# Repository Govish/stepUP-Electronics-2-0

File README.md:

# stepUP-Electronics-2-0
 New Electronics Suite for the stepUP 3D Printer!
 New Electronics include:
  - An updated LCD control panel loosely based off the Panelolu2
  - New printer mainboard
     - Arduino DUE printer controller running Marlin 2.0
     - ESP32 acting as WiFi server through ESP3D
     - Multiplexed SD card allowing read/write access to both the ESP32 and the Arduino DUE
     - TMC2130 Stepper Drivers with SPI configuration and connected diagnostic pins
     - RGB LED light strip control
     - High-power 20A heated bed control
     - ATX PSU control
  - Black ribbon cable wiring all throughout the machine with PCB breakouts
     - Full connectorization

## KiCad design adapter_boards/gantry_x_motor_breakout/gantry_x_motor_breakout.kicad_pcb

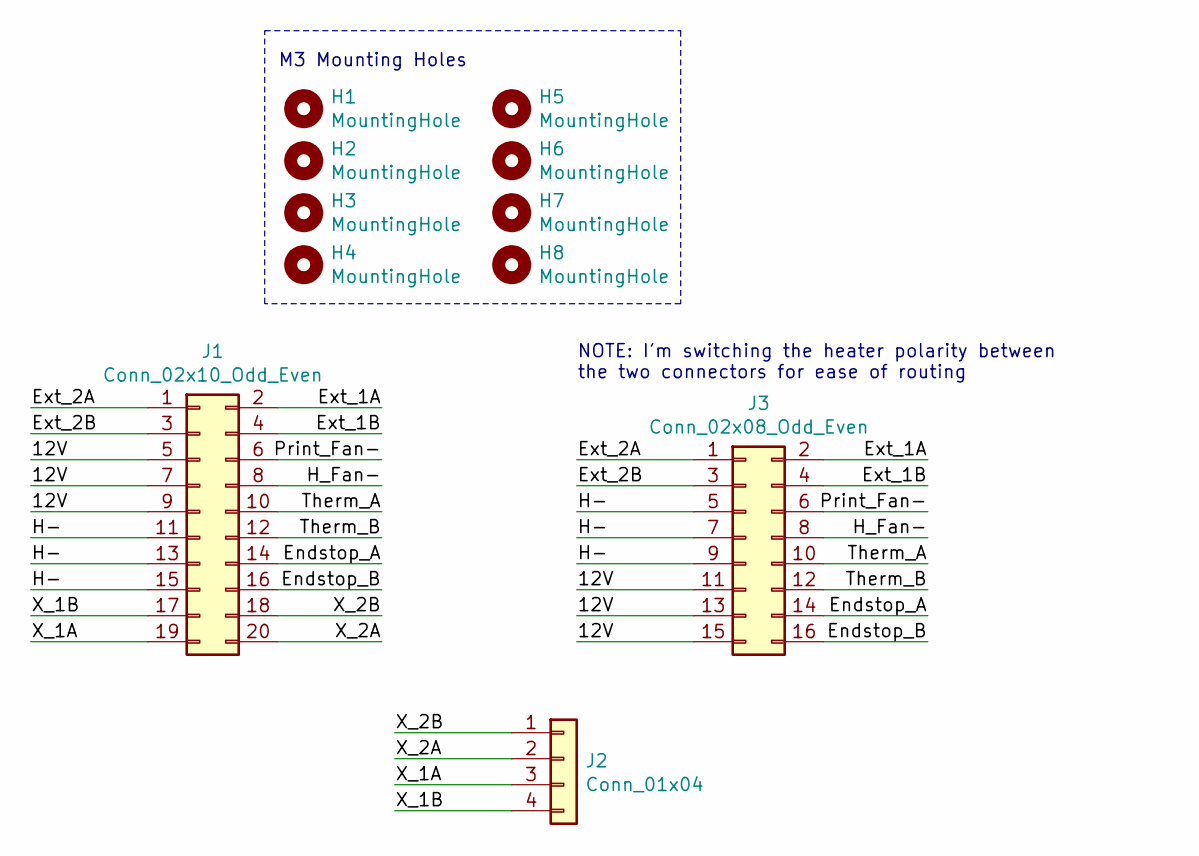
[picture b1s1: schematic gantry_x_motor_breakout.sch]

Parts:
H1, H2, H3, H4, H5, H6, H7, H8: MountingHole; MountingHole_3.2mm_M3_Pad
J1: Conn_02x10_Odd_Even; IDC-Header_2x10_P2.54mm_Vertical
J2: Conn_01x04; JST_XH_B4B-XH-A_1x04_P2.50mm_Vertical
J3: Conn_02x08_Odd_Even; IDC-Header_2x08_P2.54mm_Vertical

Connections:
/12V: J1.5, J1.7, J1.9, J3.11, J3.13, J3.15
/Endstop_A: J1.14, J3.14
/Endstop_B: J1.16, J3.16
/Ext_1A: J1.2, J3.2
/Ext_1B: J1.4, J3.4
/Ext_2A: J1.1, J3.1
/Ext_2B: J1.3, J3.3
/H-: J1.11, J1.13, J1.15, J3.5, J3.7, J3.9
/H_Fan-: J1.8, J3.8
/Print_Fan-: J1.6, J3.6
/Therm_A: J1.10, J3.10
/Therm_B: J1.12, J3.12
/X_1A: J1.19, J2.3
/X_1B: J1.17, J2.4
/X_2A: J1.20, J2.2
/X_2B: J1.18, J2.1

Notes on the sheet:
M3 Mounting Holes
NOTE: I'm switching the heater polarity between the two connectors for ease of routing

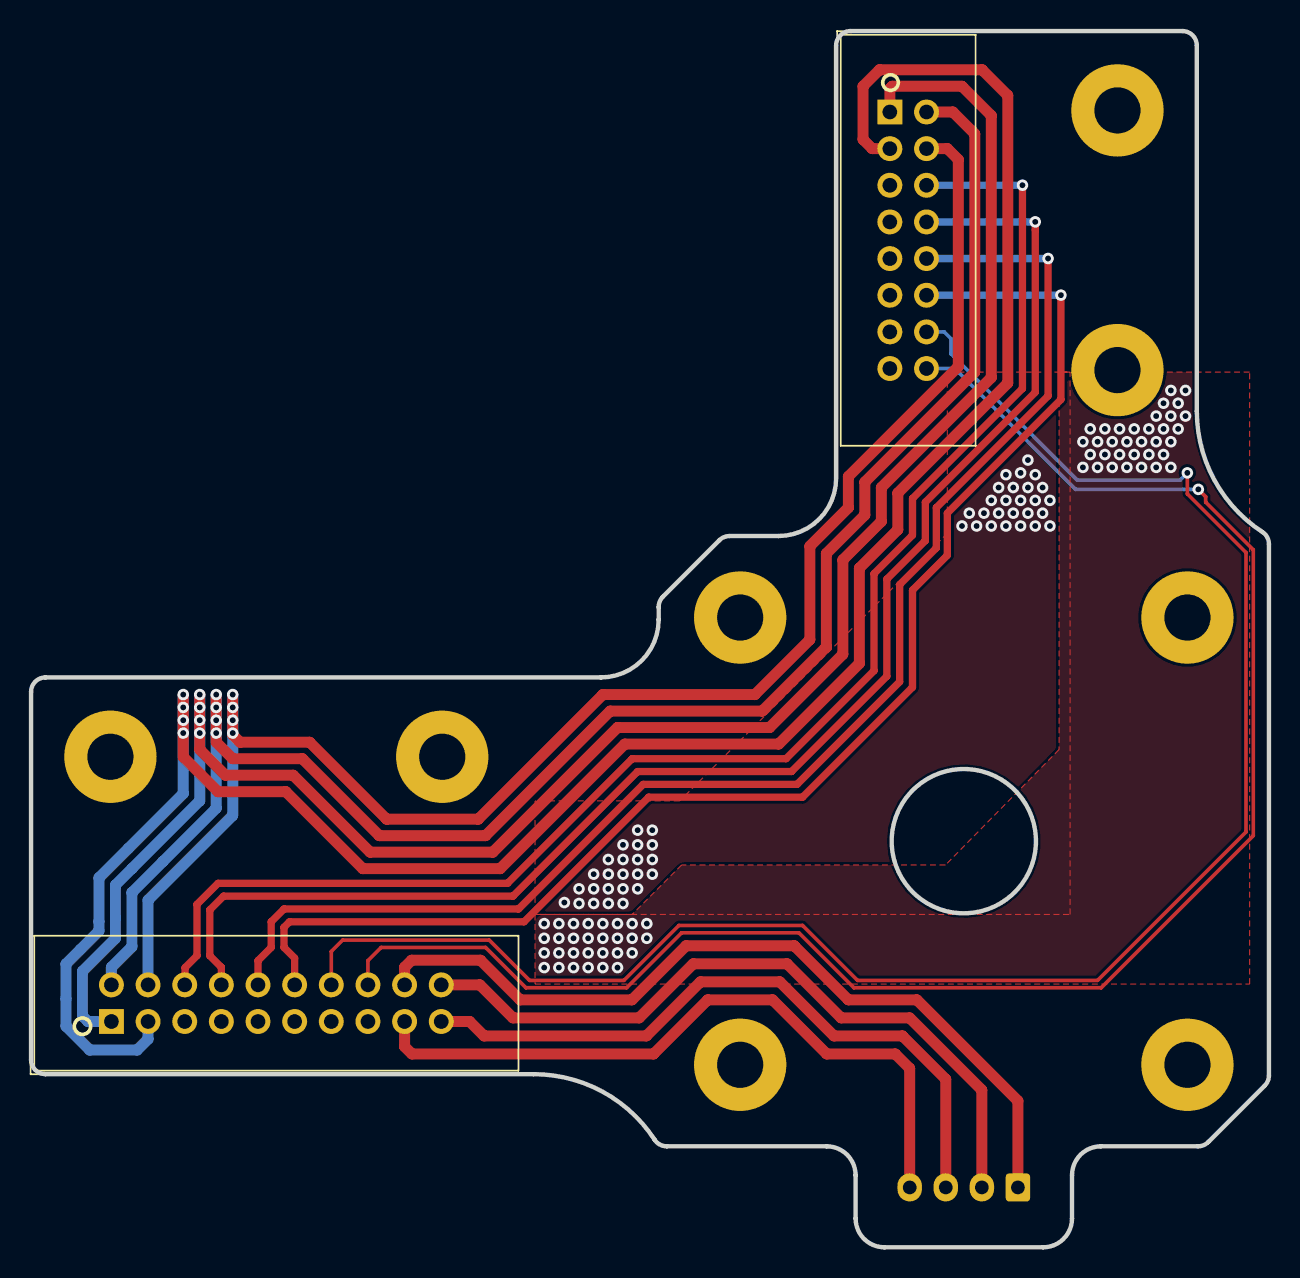
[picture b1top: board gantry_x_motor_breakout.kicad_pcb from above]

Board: 2 copper layers, 85.8 x 84.3 mm, 11 parts (1 on the bottom side), 16 nets.

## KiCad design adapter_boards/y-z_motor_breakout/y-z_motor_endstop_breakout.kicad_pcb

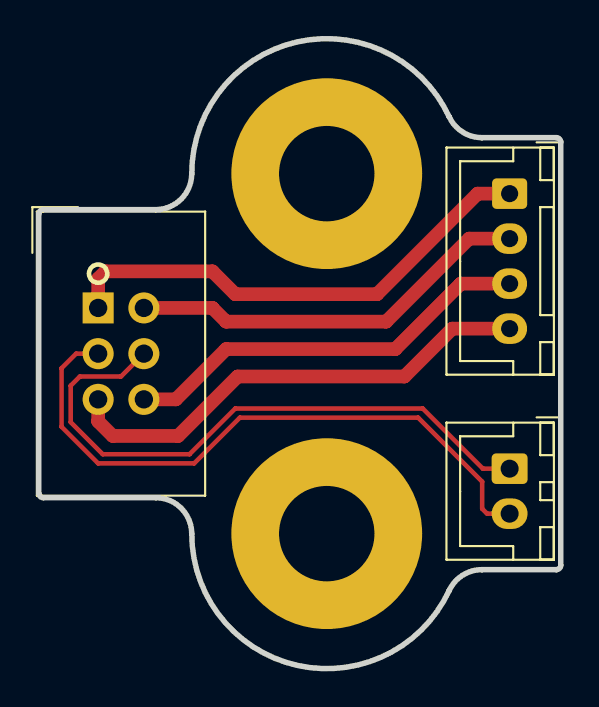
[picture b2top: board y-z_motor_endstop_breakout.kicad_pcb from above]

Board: 2 copper layers, 29.0 x 35.0 mm, 5 parts (0 on the bottom side), 6 nets.

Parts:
H1, H2: MountingHole; MountingHole_5.3mm_M5_Pad
J1: Conn_02x03_Odd_Even; IDC-Header_2x03_P2.54mm_Vertical
J2: Conn_01x04; JST_XH_B4B-XH-A_1x04_P2.50mm_Vertical
J3: Conn_01x02; JST_XH_B2B-XH-A_1x02_P2.50mm_Vertical

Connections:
unnamed: J1.1, J2.1
unnamed: J1.2, J2.2
unnamed: J1.3, J3.2
unnamed: J1.4, J3.1
unnamed: J1.5, J2.4
unnamed: J1.6, J2.3

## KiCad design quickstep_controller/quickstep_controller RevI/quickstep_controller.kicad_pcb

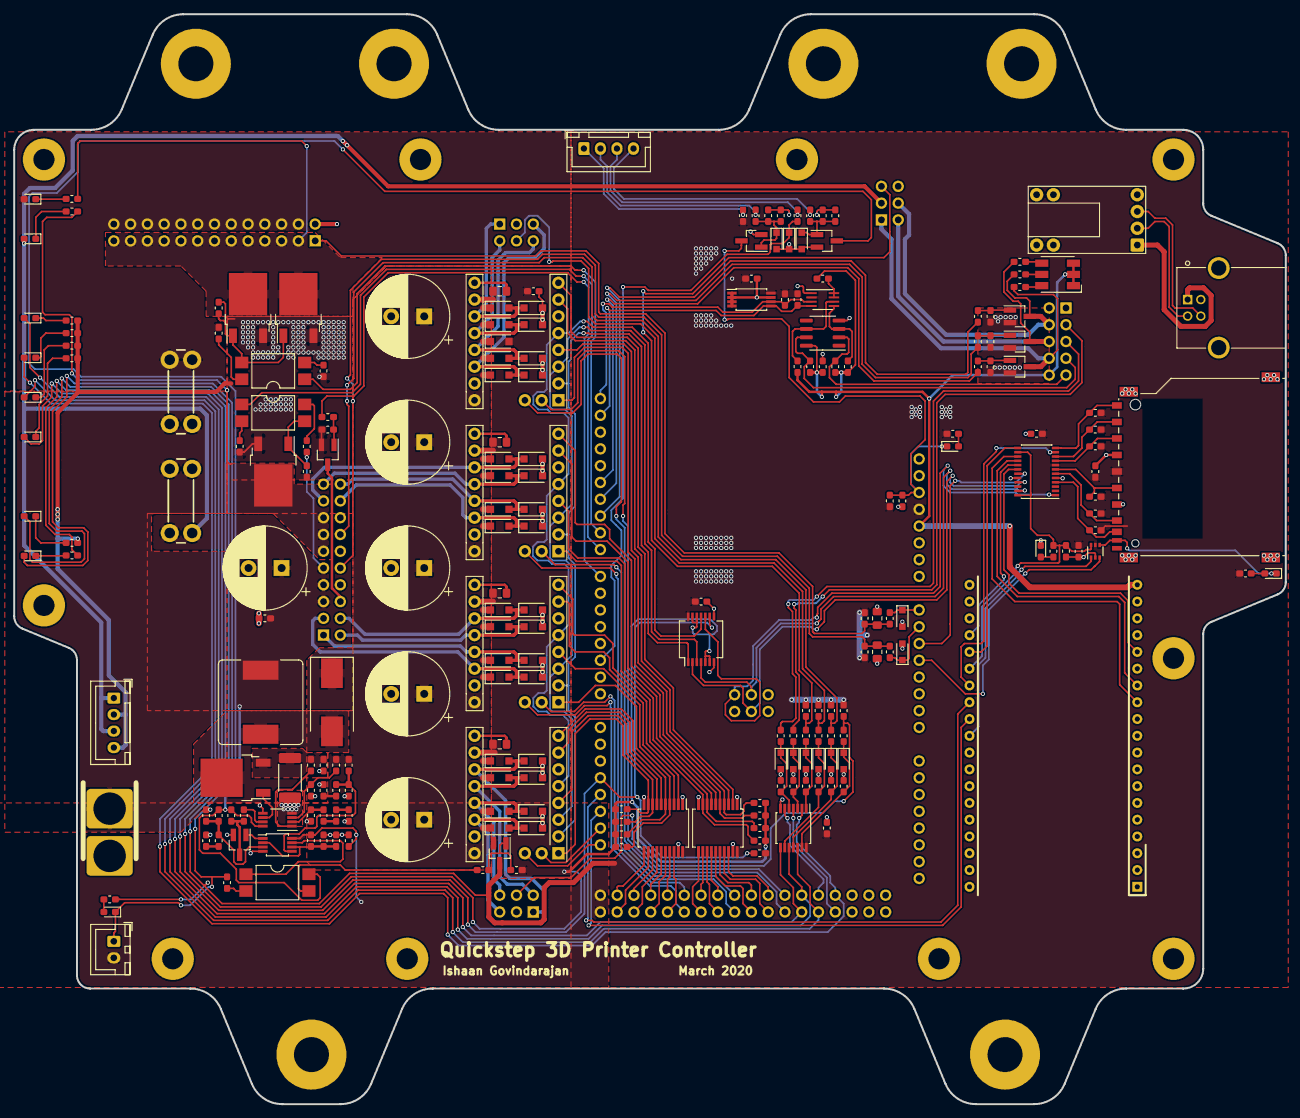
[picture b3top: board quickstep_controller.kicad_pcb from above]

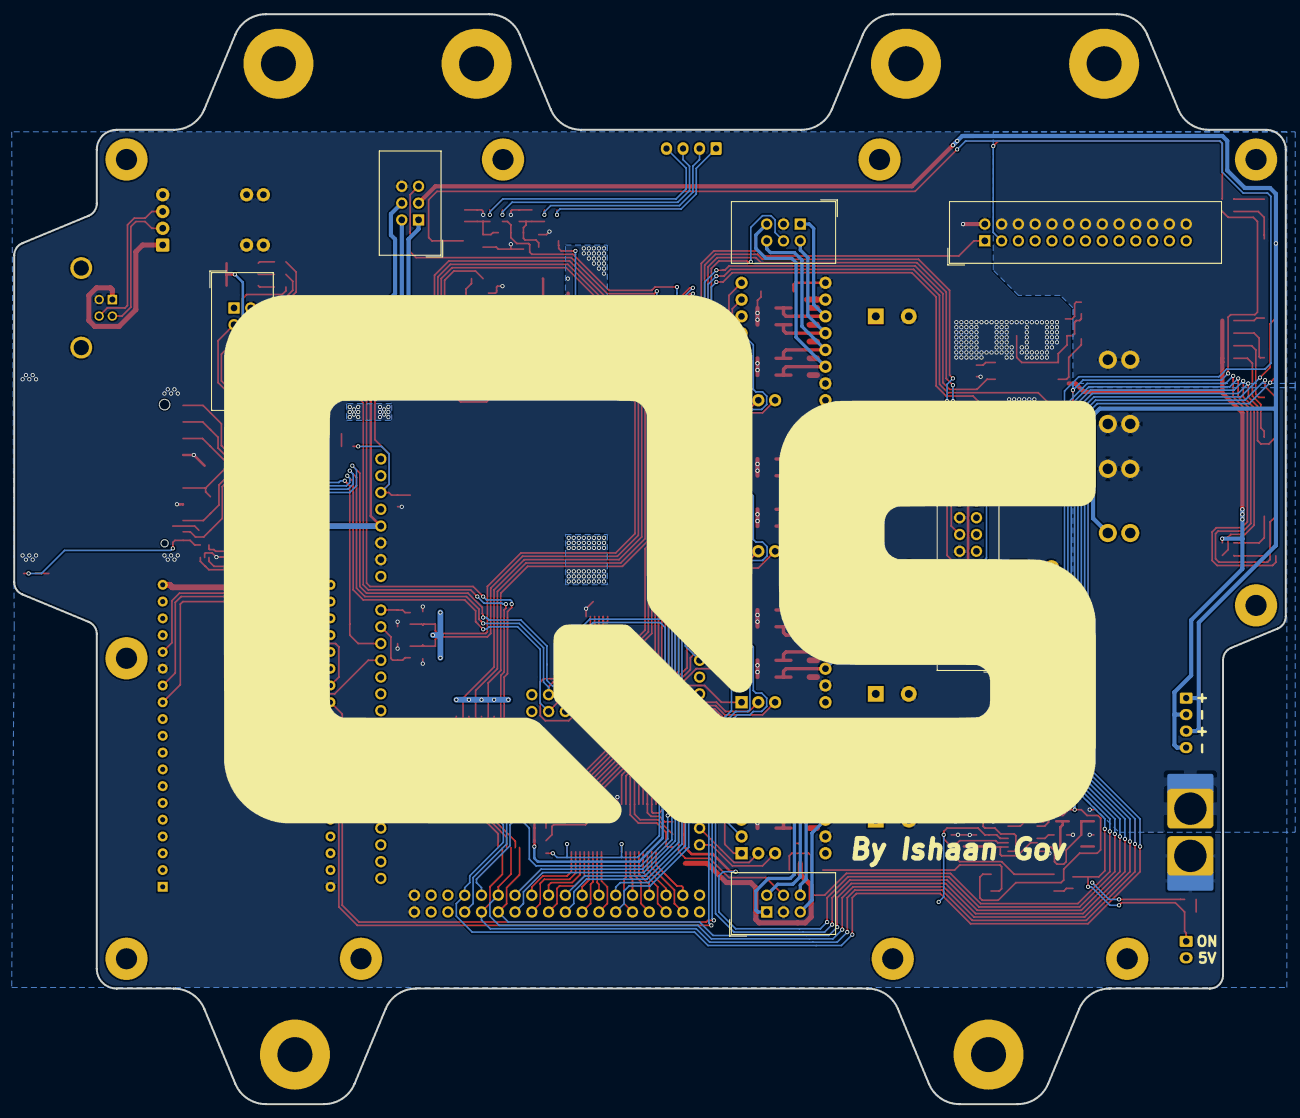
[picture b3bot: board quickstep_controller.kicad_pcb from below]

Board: 2 copper layers, 192.5 x 165.0 mm, 252 parts (8 on the bottom side), 188 nets.

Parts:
C201, C202, C203, C401, C402, C403, C404, C405, C406, C407, C408, C501, C502, C709, C801, C803, C804, C807, C809, C1201, C1202: 100n; C_0603_1608Metric_Pad1.05x0.95mm_HandSolder
C301, C302, C701, C703, C705, C707: 4u7; C_0805_2012Metric_Pad1.15x1.40mm_HandSolder
C702, C704, C706, C708, C802, C810: 470u; CP_Radial_D12.5mm_P5.00mm
C805: 270p; C_0603_1608Metric_Pad1.05x0.95mm_HandSolder
C806: 4.7n; C_0603_1608Metric_Pad1.05x0.95mm_HandSolder
C808: 10p; C_0603_1608Metric_Pad1.05x0.95mm_HandSolder
D201, D202, D301, D302, D405, D406, D407, D408, D409, D410, D702, D703: RED; LED_0603_1608Metric_Pad1.05x0.95mm_HandSolder
D303, D304, D401, D402, D403, D404, D411, D412, D413, D1201, D1202: 3.6V; D_SOD-323_HandSoldering
D501: 150505M173300; LED_RGB_5050-6
D701, D901, D902, D903, D904, D905, D906, D907, D908, D1001, D1002, D1003, D1004, D1005, D1006, D1007, D1008, D1401, D1402, D1403, D1404, D1405, D1406, D1407, D1408, D1409, D1410, D1411, D1412, D1413, D1414, D1415, D1416: DSS15UTR; D_SOD-123F
D801: CDBC380-G; D_SMC_Handsoldering
F1501: 7.5A; Keystone_3557
F1502: 25A; Keystone_3557
G101: Quickstep Logo; qs_logo
H101, H102, H103, H104, H105, H106, H107, H108, H109, H110: M3; MountingHole_3.2mm_M3_Pad
H111, H112, H113, H114, H115, H116: M5; MountingHole_5.3mm_M5_Pad
J101, J1502: Conn_01x04; JST_XH_B4B-XH-A_1x04_P2.50mm_Vertical
J201: SD_Card; SD_TE_2041021
J601: USB_A; USB_Adapter
J602: USB_B; CUI_UJ2-BH-W1-TH
J901, J1001, J1301: Conn_02x03_Odd_Even; IDC-Header_2x03_P2.54mm_Vertical
J1101: Conn_02x13_Odd_Even; IDC-Header_2x13_P2.54mm_Vertical
J1201: Conn_02x05_Odd_Even; IDC-Header_2x05_P2.54mm_Vertical
J1401: Conn_02x10_Odd_Even; IDC-Header_2x10_P2.54mm_Vertical
J1501: Conn_01x02; JST_XH_B2B-XH-A_1x02_P2.50mm_Vertical
J1503: Conn_XT; XT60-Male
L801: 4.7uH; L_Bourns_SRR1260
Q301, Q302, Q304, Q802: AOD514; TO-252-2
Q303, Q401, Q402, Q501, Q502, Q503, Q701, Q801: NTR3C21NZT1G; SOT-23_Handsoldering
R201, R202, R301, R302, R409, R410, R411, R412, R413, R417, R418, R419, R420, R421, R514, R515, R516, R712, R715, R803, R805, R807, R808, R816: 1K; R_0603_1608Metric_Pad1.05x0.95mm_HandSolder
R203, R204, R205, R206, R207, R208, R209, R401, R402, R403, R404, R405, R406, R407, R408, R414, R701, R702, R703, R704, R705, R706, R707, R708, R710, R713, R714, R804, R809, R810, R811, R1201, R1202: 10K; R_0603_1608Metric_Pad1.05x0.95mm_HandSolder
R303, R311, R312, R506, R507, R508, R509, R510, R709, R711: 390; R_0603_1608Metric_Pad1.05x0.95mm_HandSolder
R304, R306: 390R; R_0603_1608Metric_Pad1.05x0.95mm_HandSolder
R305, R307, R308, R415, R416, R503, R511, R512, R513: 240K; R_0603_1608Metric_Pad1.05x0.95mm_HandSolder
R309, R310, R313, R314, R501, R502, R504, R505: 4K7; R_0603_1608Metric_Pad1.05x0.95mm_HandSolder
R801, R806, R812: 16.9K; R_0603_1608Metric_Pad1.05x0.95mm_HandSolder
R802: 4.7K; R_0603_1608Metric_Pad1.05x0.95mm_HandSolder
R813: 100R; R_0603_1608Metric_Pad1.05x0.95mm_HandSolder
R814: 7mR; R_2512_6332Metric_Pad1.52x3.35mm_HandSolder
R815: 22.6K; R_0603_1608Metric_Pad1.05x0.95mm_HandSolder
U201: TS3A27518E; TSSOP-24_4.4x7.8mm_P0.65mm
U202: SN74LVC1G3157DCK3; SOT-363_SC-70-6
U301, U302, U708: LTV-817S; SMDIP-4_W9.53mm
U401: 74HC14; TSSOP-14_4.4x5mm_P0.65mm
U501: PCA9306; SSOP-8_2.95x2.8mm_P0.65mm
U502: P82B715; SOIC-8_3.9x4.9mm_P1.27mm
U503: 24LC256; TSSOP-8_4.4x3mm_P0.65mm
U601: ESP-32_DEVBOARD; ESP32
U701, U702, U703, U704: StepStick-TMC2130; TMC-21x0
U705: 4066; SSOP-14_5.3x6.2mm_P0.65mm
U706, U707: 74HC245; SSOP-20_5.3x7.2mm_P0.65mm
U801: LM3488; VSSOP-8_3.0x3.0mm_P0.65mm
U802: LM393; MSOP-8_3x3mm_P0.65mm
XA601: Arduino_Due_Shield; Arduino_Due_Shield_noHolesSilk

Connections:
+3V3: C201.2, C202.1, C203.1, C405.2, C502.2, C709.2, D702.2, J201.4, Q701.3, R201.2, R204.2, R205.2, R206.2, R207.2, R208.2, R209.2, R313.1, R314.1, R401.1, R402.1, R403.1, R404.1, R413.2, R414.1, R417.2, R418.2, R501.2, R502.2, R710.1, U201.8, U202.5, U401.14, U501.2, U503.8, U705.14, U706.20, U707.20, XA601.3V3
+5V: C501.2, C809.2, D501.1, D501.2, D501.3, J1201.10, J1501.2, R503.1, R504.2, R505.2, R506.2, R507.2, R809.1, U502.8, U601.19, U802.8, XA601.5V1, XA601.5V3, XA601.5V4
+12V: C802.1, C803.1, D301.2, F1501.1, J1301.3, J1401.5, J1401.7, J1401.9, J1502.1, J1502.3, L801.1, R306.2, R801.1, R811.1, U708.4, U801.8
/ATX_Connections/LINE_IN: F1501.2, F1502.2, J1503.+
/ATX_Connections/PS_ON: D410.1, J1501.1, Q402.3, R715.2
/ENC_A: U401.6, XA601.D46
/ENC_B: U401.4, XA601.D49
/EXT-: J1401.11, J1401.13, J1401.15, Q302.2, R309.2
/FIL_SEN+: J901.4, R404.2, R408.1
/PRINT_FAN-: J1401.6, Q303.3
/THERM+: C302.1, J1401.10, R312.1, R314.2
/X_STOP+: J1401.14, R401.2, R405.1
/Y_STOP+: J1301.5, R402.2, R406.1
/Z_STOP+: J1001.4, R403.2, R407.1
/qs_Drivers/BUF_ECS: R704.1, U704.4, U706.4
/qs_Drivers/BUF_EDIR: U704.8, U706.2
/qs_Drivers/BUF_EEN: R708.2, U704.1, U706.5
/qs_Drivers/BUF_ESTEP: U704.7, U706.3
/qs_Drivers/BUF_XCS: R701.1, U701.4, U707.8
/qs_Drivers/BUF_XDIR: U701.8, U707.6
/qs_Drivers/BUF_XEN: R705.2, U701.1, U707.9
/qs_Drivers/BUF_XSTEP: U701.7, U707.7
/qs_Drivers/BUF_YCS: R702.1, U702.4, U707.4
/qs_Drivers/BUF_YDIR: U702.8, U707.2
/qs_Drivers/BUF_YEN: R706.2, U702.1, U707.5
/qs_Drivers/BUF_YSTEP: U702.7, U707.3
/qs_Drivers/BUF_ZCS: R703.1, U703.4, U706.8
/qs_Drivers/BUF_ZDIR: U703.8, U706.6
/qs_Drivers/BUF_ZEN: R707.2, U703.1, U706.9
/qs_Drivers/BUF_ZSTEP: U703.7, U706.7
/qs_Drivers/DUE_MISO: U201.1, U705.10, XA601.MISO
/qs_Drivers/DUE_MOSI: U201.21, U705.2, XA601.MOSI
/qs_Drivers/DUE_SCK: U201.23, U705.4, XA601.SCK
/qs_Drivers/DUE_VMOT_GOOD: R709.1, R710.2, U705.9, U706.19, U707.19, XA601.D17
/qs_Drivers/ECS: U706.16, XA601.D27
/qs_Drivers/EDIAG0: U704.18, XA601.D30
/qs_Drivers/EDIAG1: U704.17, XA601.D31
/qs_Drivers/EDIR: U706.18, XA601.D29
/qs_Drivers/EEN: U706.15, XA601.D26
/qs_Drivers/ESTEP: U706.17, XA601.D28
/qs_Drivers/VMOT_GOOD: U708.1, U802.7
/qs_Drivers/XCS: U707.12, XA601.D32
/qs_Drivers/XDIAG0: U701.18, XA601.D36
/qs_Drivers/XDIAG1: U701.17, XA601.D37
/qs_Drivers/XDIR: U707.14, XA601.D34
/qs_Drivers/XEN: U707.11, XA601.D33
/qs_Drivers/XSTEP: U707.13, XA601.D35
/qs_Drivers/X_1A: D1403.2, D1404.1, J1401.19, U701.12
/qs_Drivers/X_1B: D1407.2, D1408.1, J1401.17, U701.11
/qs_Drivers/X_2A: D1415.2, D1416.1, J1401.20, U701.13
/qs_Drivers/X_2B: D1411.2, D1412.1, J1401.18, U701.14
/qs_Drivers/YCS: U707.16, XA601.D38
/qs_Drivers/YDIAG0: U702.18, XA601.D42
/qs_Drivers/YDIAG1: U702.17, XA601.D43
/qs_Drivers/YDIR: U707.18, XA601.D40
/qs_Drivers/YEN: U707.15, XA601.D39
/qs_Drivers/YSTEP: U707.17, XA601.D41
/qs_Drivers/ZCS: U706.12, XA601.D23
/qs_Drivers/ZDIAG0: U703.18, XA601.D20
/qs_Drivers/ZDIAG1: U703.17, XA601.D21
/qs_Drivers/ZDIR: U706.14, XA601.D25
/qs_Drivers/ZEN: U706.11, XA601.D22
/qs_Drivers/ZSTEP: U706.13, XA601.D24
/qs_Drivers/_MISO: U701.5, U702.5, U703.5, U704.5, U705.11
/qs_Drivers/_MOSI: U701.2, U702.2, U703.2, U704.2, U705.1
/qs_Drivers/_SCK: U701.3, U702.3, U703.3, U704.3, U705.3
/qs_I2C_LEDs/B_DRAIN: J1201.8, J1301.1, Q503.3, R516.2
/qs_I2C_LEDs/B_PWM: R510.2, XA601.D12
/qs_I2C_LEDs/DUE_SCL: R501.1, U501.3, U503.6, XA601.SCL1
/qs_I2C_LEDs/DUE_SDA: R502.1, U501.4, U503.5, XA601.SDA1
/qs_I2C_LEDs/G_DRAIN: J1201.6, J1301.2, Q502.3, R514.2
/qs_I2C_LEDs/LCL: J1201.7, R507.1, U502.7
/qs_I2C_LEDs/LDA: J1201.9, R506.1, U502.2
/qs_LCD/LED_RED: J1201.4, J1301.4, Q501.3, R515.2
/qs_Processors/D+: J601.3, J602.3
/qs_Processors/D-: J601.2, J602.2
/qs_Processors/DUE_EXT_HEAT: U302.1, XA601.D8
/qs_Processors/DUE_EXT_THERM: D304.1, R312.2, XA601.A1
/qs_Processors/DUE_LED_GREEN: R509.2, XA601.D11
/qs_Processors/DUE_LED_RED: R508.2, XA601.D10
/qs_Processors/DUE_PC_FAN: R303.2, XA601.D7
/qs_Processors/DUE_PSON: D413.1, R420.2, XA601.D2
/qs_Processors/DUE_RESET: C406.2, D409.1, Q401.3, R414.2, XA601.RST1
/qs_Processors/ESP_CD: U202.1, U601.29
/qs_Processors/ESP_CLK: U201.15, U601.12
/qs_Processors/ESP_CMD: U201.17, U601.23
/qs_Processors/ESP_D0: U201.13, U601.24
/qs_Processors/ESP_D1: U201.11, U601.26
/qs_Processors/ESP_D2: U201.16, U601.13
/qs_Processors/ESP_D3: U201.18, U601.15
/qs_Processors/ESP_RX: U601.27, XA601.D18
/qs_Processors/ESP_SD_SEL: R202.2, R203.2, U201.14, U201.24, U202.6, U601.25
/qs_Processors/ESP_TX: U601.28, XA601.D19
/qs_Processors/FIL_RUNOUT: D408.2, U401.8, XA601.D45
/qs_Processors/X_STOP: D405.2, U401.10, XA601.D44
/qs_Processors/Y_STOP: D406.2, U401.2, XA601.D48
/qs_Processors/Z_STOP: D407.2, U401.12, XA601.D47
/qs_SD_Interface/CARD_DETECT: D202.1, J201.10, U202.4
/qs_SD_Interface/CLK: J201.5, R207.1, U201.7
/qs_SD_Interface/CMD: J201.2, R206.1, U201.9
/qs_SD_Interface/D0: J201.7, R208.1, U201.6
/qs_SD_Interface/D1: J201.8, R209.1, U201.4
/qs_SD_Interface/D2: J201.9, R204.1, U201.12
/qs_SD_Interface/D3: J201.1, R205.1, U201.10
/qs_SD_Interface/DUE_CD: U202.3, XA601.A3
/qs_SD_Interface/DUE_CS: U201.19, XA601.A2
/qs_Switches/E_PS_ON_IN: J101.4, R421.1
/qs_Switches/E_PS_ON_OUT: J101.3, R420.1
/qs_Switches/E_RST_IN: J101.2, R419.1
/qs_Switches/E_RST_OUT: J101.1, R418.1
/qs_Temp_Control/BED_HEAT: U301.1, XA601.D9
/qs_Temp_Control/BED_THERM: D303.1, R311.2, XA601.A0
/qs_bed_conn/BED-: J1101.3, J1101.5, J1101.7, J1101.9, J1101.11, J1101.13, J1101.15, J1101.17, J1101.19, J1101.21, J1101.23, J1101.25, Q301.2, Q304.2, R310.2
/qs_bed_conn/THERM+: C301.1, J1101.1, R311.1, R313.2
/qs_gantry_conn/EXT_1A: D1413.2, D1414.1, J1401.2, U704.12
/qs_gantry_conn/EXT_1B: D1409.2, D1410.1, J1401.4, U704.11
/qs_gantry_conn/EXT_2A: D1401.2, D1402.1, J1401.1, U704.13
/qs_gantry_conn/EXT_2B: D1405.2, D1406.1, J1401.3, U704.14
/qs_power/EN_CONV: Q801.1, U802.1
/qs_power/SENSE: C808.1, Q802.3, R813.2, R814.1
/qs_power/SWITCH: D801.2, L801.2, Q802.2
/qs_ymotor_fil/YMOT_1A: D905.2, D906.1, J901.2, U702.12
/qs_ymotor_fil/YMOT_1B: D901.2, D902.1, J901.1, U702.11
/qs_ymotor_fil/YMOT_2A: D907.2, D908.1, J901.6, U702.13
/qs_ymotor_fil/YMOT_2B: D903.2, D904.1, J901.5, U702.14
/qs_zmotor_stop/ZMOT_1A: D1005.2, D1006.1, J1001.2, U703.12
/qs_zmotor_stop/ZMOT_1B: D1001.2, D1002.1, J1001.1, U703.11
/qs_zmotor_stop/ZMOT_2A: D1007.2, D1008.1, J1001.6, U703.13
/qs_zmotor_stop/ZMOT_2B: D1003.2, D1004.1, J1001.5, U703.14
GND: C201.1, C202.2, C203.2, C301.2, C302.2, C401.2, C402.2, C403.2, C404.2, C405.1, C406.1, C407.1, C408.1, C501.1, C502.1, C701.1, C702.2, C703.1, C704.2, C705.1, C706.2, C707.1, C708.2, C709.1, C801.1, C802.2, C803.2, C804.1, C805.1, C807.1, C808.2, C809.1, C810.2, C1201.2, C1202.2, D201.1, D303.2, D304.2, D401.2, D402.2, D403.2, D404.2, D411.2, D412.2, D413.2, D902.2, D904.2, D906.2, D908.2, D1002.2, D1004.2, D1006.2, D1008.2, D1201.2, D1202.2, D1402.2, D1404.2, D1406.2, D1408.2, D1410.2, D1412.2, D1414.2, D1416.2, J201.3, J201.6, J201.12, J601.4, J601.5, J602.4, J602.5, J901.3, J1001.3, J1101.2, J1201.2, J1301.6, J1401.8, J1401.12, J1401.16, J1502.2, J1502.4, J1503.-, Q301.3, Q302.3, Q303.2, Q304.3, Q401.2, Q402.2, Q501.2, Q502.2, Q503.2, Q801.2, R203.1, R301.2, R302.2, R305.1, R307.1, R308.1, R409.1, R410.1, R411.1, R412.1, R415.1, R416.1, R511.1, R512.1, R513.1, R711.1, R712.2, R803.2, R805.2, R808.2, R810.2, R814.2, R816.2, U201.5, U201.20, U202.2, U401.7, U501.1, U502.4, U503.1, U503.2, U503.3, U503.4, U503.7, U601.14, U601.32, U601.38, U701.9, U701.15, U702.9, U702.15, U703.9, U703.15, U704.9, U704.15, U705.7, U705.8, U706.1, U706.10, U707.1, U707.10, U801.4, U801.5, U802.4, XA601.GND2, XA601.GND3, XA601.GND5, XA601.GND6
unnamed: C401.1, D401.1, R405.2, U401.11
unnamed: C402.1, D402.1, R406.2, U401.1
unnamed: C403.1, D403.1, R407.2, U401.13
unnamed: C404.1, D404.1, R408.2, U401.9
unnamed: C407.2, D411.1, Q401.1, R415.2, R419.2
unnamed: C408.2, D412.1, Q402.1, R416.2, R421.2
unnamed: C801.2, R801.2, R802.1, U802.3
unnamed: C804.2, R806.2, R807.1, U802.5
unnamed: C805.2, C806.1, U801.2
unnamed: C806.2, R804.1
unnamed: C807.2, R809.2, R810.1, U802.2, U802.6
unnamed: C1201.1, D1201.1, R1201.2, U401.3
unnamed: C1202.1, D1202.1, R1202.2, U401.5
unnamed: D201.2, R202.1
unnamed: D202.2, R201.1
unnamed: D301.1, R309.1
unnamed: D302.1, R310.1
unnamed: D405.1, R409.2
unnamed: D406.1, R410.2
unnamed: D407.1, R411.2
unnamed: D408.1, R412.2
unnamed: D409.2, R413.1
unnamed: D410.2, R417.1
unnamed: D501.4, R514.1
unnamed: D501.5, R515.1
unnamed: D501.6, R516.1
unnamed: D702.1, R709.2
unnamed: D703.1, R711.2
unnamed: J601.1, J602.1
unnamed: J1201.3, R1201.1
unnamed: J1201.5, R1202.1
unnamed: Q301.1, Q304.1, R305.2, U301.3
unnamed: Q302.1, R307.2, U302.3
unnamed: Q303.1, R303.1, R308.2
unnamed: Q501.1, R508.1, R511.2
unnamed: Q502.1, R509.1, R512.2
unnamed: Q503.1, R510.1, R513.2
unnamed: Q701.1, R713.1, R714.2
unnamed: Q801.3, R811.2, R812.2
unnamed: Q802.1, U801.6
unnamed: R301.1, U301.2
unnamed: R302.1, U302.2
unnamed: R304.1, U301.4
unnamed: R306.1, U302.4
unnamed: R503.2, U501.7, U501.8
unnamed: R504.1, U501.5, U502.3
unnamed: R505.1, U501.6, U502.6
unnamed: R713.2, U708.3
unnamed: R715.1, U708.2
unnamed: R802.2, R803.1
unnamed: R804.2, R805.1
unnamed: R807.2, R808.1
unnamed: R812.1, U801.7
unnamed: R813.1, U801.1
unnamed: R815.2, R816.1, U801.3
VBUS: C702.1, C704.1, C706.1, C708.1, C810.1, D701.1, D801.1, D901.1, D903.1, D905.1, D907.1, D1001.1, D1003.1, D1005.1, D1007.1, D1401.1, D1403.1, D1405.1, D1407.1, D1409.1, D1411.1, D1413.1, D1415.1, R806.1, R815.1, U701.16, U702.16, U703.16, U704.16
VCC: C701.2, C703.2, C705.2, C707.2, D701.2, D703.2, Q701.2, R701.2, R702.2, R703.2, R704.2, R705.1, R706.1, R707.1, R708.1, R712.1, R714.1, U701.10, U702.10, U703.10, U704.10, U705.5, U705.6, U705.12, U705.13
VPP: D302.2, F1502.1, J1101.4, J1101.6, J1101.8, J1101.10, J1101.12, J1101.14, J1101.16, J1101.18, J1101.20, J1101.22, J1101.24, J1101.26, R304.2

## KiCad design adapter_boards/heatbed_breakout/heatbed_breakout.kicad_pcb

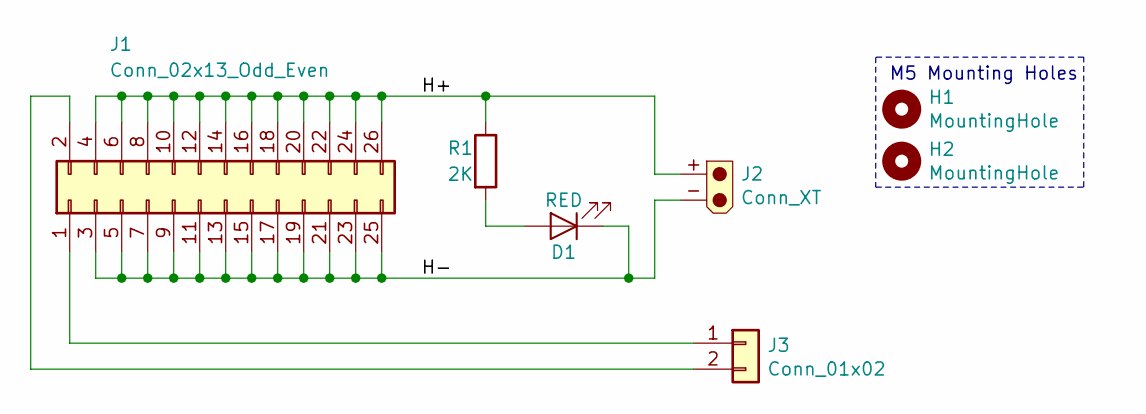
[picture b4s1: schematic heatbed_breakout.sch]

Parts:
D1: RED; LED_0603_1608Metric_Pad1.05x0.95mm_HandSolder
H1, H2: MountingHole; MountingHole_5.3mm_M5_Pad
J1: Conn_02x13_Odd_Even; IDC-Header_2x13_P2.54mm_Vertical
J2: Conn_XT; XT60-Female
J3: Conn_01x02; JST_XH_B2B-XH-A_1x02_P2.50mm_Vertical
R1: 2K; R_0603_1608Metric_Pad1.05x0.95mm_HandSolder

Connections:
/H+: J1.4, J1.6, J1.8, J1.10, J1.12, J1.14, J1.16, J1.18, J1.20, J1.22, J1.24, J1.26, J2.+, R1.1
/H-: D1.1 (K), J1.3, J1.5, J1.7, J1.9, J1.11, J1.13, J1.15, J1.17, J1.19, J1.21, J1.23, J1.25, J2.-
unnamed: D1.2 (A), R1.2
unnamed: J1.1, J3.1
unnamed: J1.2, J3.2

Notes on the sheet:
M5 Mounting Holes

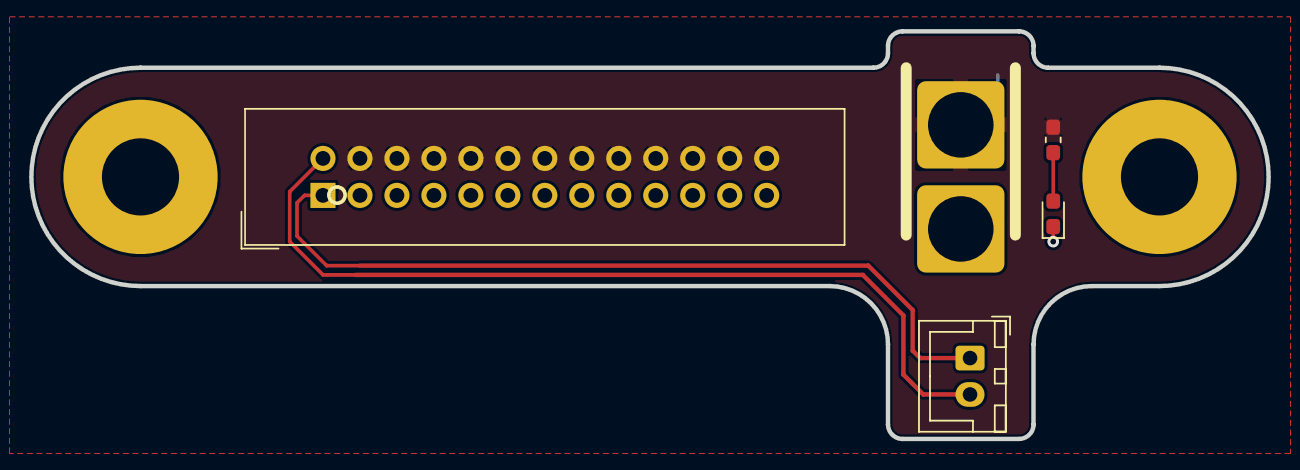
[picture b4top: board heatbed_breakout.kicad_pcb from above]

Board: 2 copper layers, 85.0 x 28.0 mm, 7 parts (0 on the bottom side), 5 nets.

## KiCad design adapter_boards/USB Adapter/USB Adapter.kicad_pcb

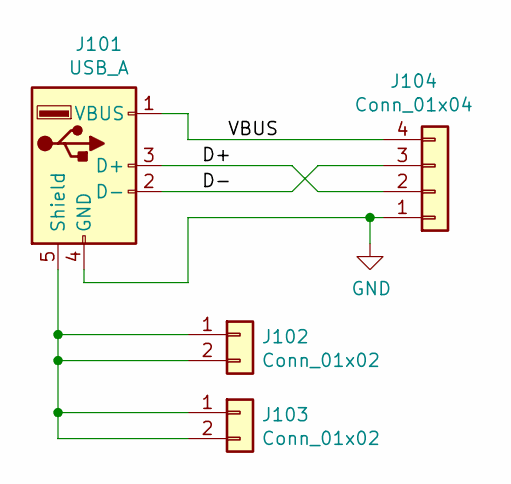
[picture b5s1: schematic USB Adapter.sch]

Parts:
J101: USB_A; USB_A_CNC_Tech-1001-008B-01001
J102, J103: Conn_01x02; PinHeader_1x02_P2.54mm_Vertical
J104: Conn_01x04; PinHeader_1x04_P2.54mm_Vertical

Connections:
/D+: J101.3 (D+), J104.2
/D-: J101.2 (D-), J104.3
/VBUS: J101.1 (VBUS), J104.4
GND: J101.4 (GND), J104.1
unnamed: J101.5 (Shield), J102.1, J102.2, J103.1, J103.2

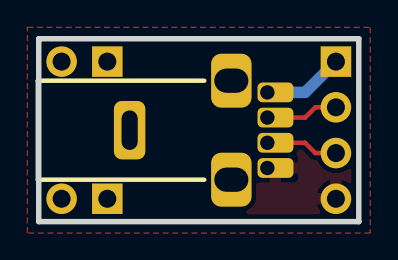
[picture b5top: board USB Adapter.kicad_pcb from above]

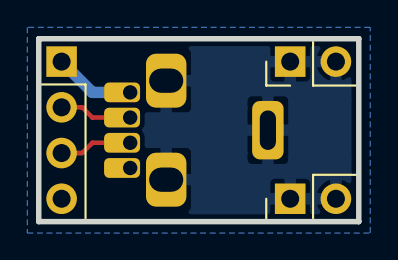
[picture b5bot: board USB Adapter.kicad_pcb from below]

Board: 2 copper layers, 17.8 x 10.2 mm, 4 parts (3 on the bottom side), 5 nets.

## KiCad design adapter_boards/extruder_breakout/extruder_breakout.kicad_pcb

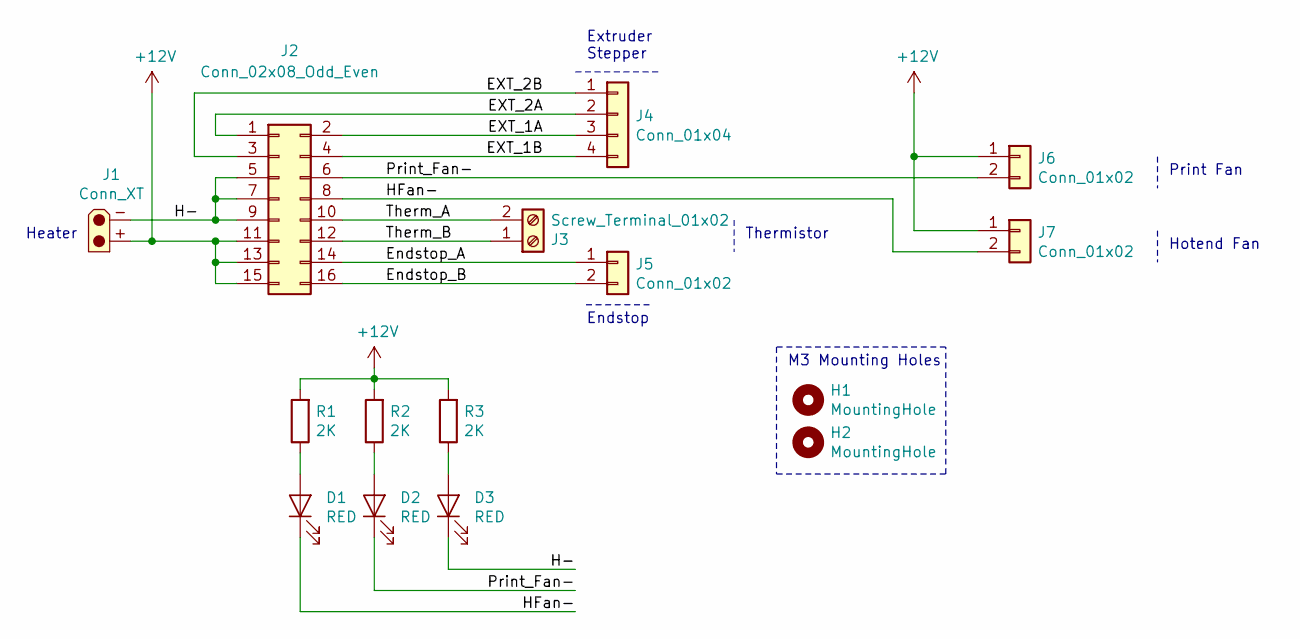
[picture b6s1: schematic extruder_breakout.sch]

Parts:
D1, D2, D3: RED; LED_0603_1608Metric_Pad1.05x0.95mm_HandSolder
H1, H2: MountingHole; MountingHole_3.2mm_M3_Pad
J1: Conn_XT; XT30U-F
J2: Conn_02x08_Odd_Even; IDC-Header_2x08_P2.54mm_Vertical
J3: Screw_Terminal_01x02; TerminalBlock_TE_2.54mmx02
J4: Conn_01x04; JST_XH_B4B-XH-A_1x04_P2.50mm_Vertical
J5, J6, J7: Conn_01x02; JST_XH_B2B-XH-A_1x02_P2.50mm_Vertical
R1, R2, R3: 2K; R_0603_1608Metric_Pad1.05x0.95mm_HandSolder

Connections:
+12V: J1.+, J2.11, J2.13, J2.15, J6.1, J7.1, R1.2, R2.2, R3.2
/EXT_1A: J2.2, J4.3
/EXT_1B: J2.4, J4.4
/EXT_2A: J2.1, J4.2
/EXT_2B: J2.3, J4.1
/Endstop_A: J2.14, J5.1
/Endstop_B: J2.16, J5.2
/H-: D3.1 (K), J1.-, J2.5, J2.7, J2.9
/HFan-: D1.1 (K), J2.8, J7.2
/Print_Fan-: D2.1 (K), J2.6, J6.2
/Therm_A: J2.10, J3.2
/Therm_B: J2.12, J3.1
unnamed: D1.2 (A), R1.1
unnamed: D2.2 (A), R2.1
unnamed: D3.2 (A), R3.1

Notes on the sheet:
Print Fan
Hotend Fan
Heater
Endstop
Extruder Stepper
Thermistor
M3 Mounting Holes

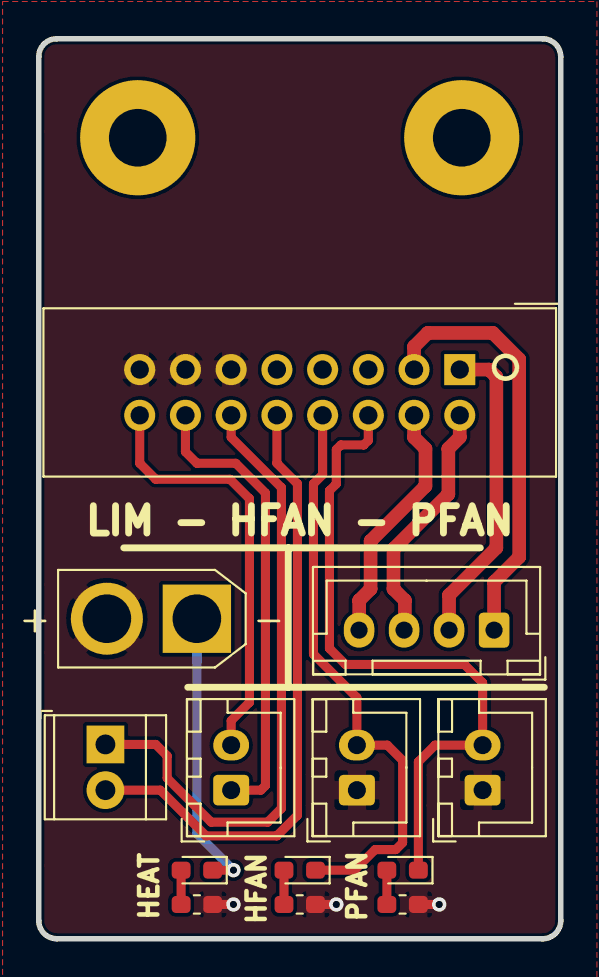
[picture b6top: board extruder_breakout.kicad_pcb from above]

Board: 2 copper layers, 29.0 x 50.0 mm, 15 parts (0 on the bottom side), 15 nets.

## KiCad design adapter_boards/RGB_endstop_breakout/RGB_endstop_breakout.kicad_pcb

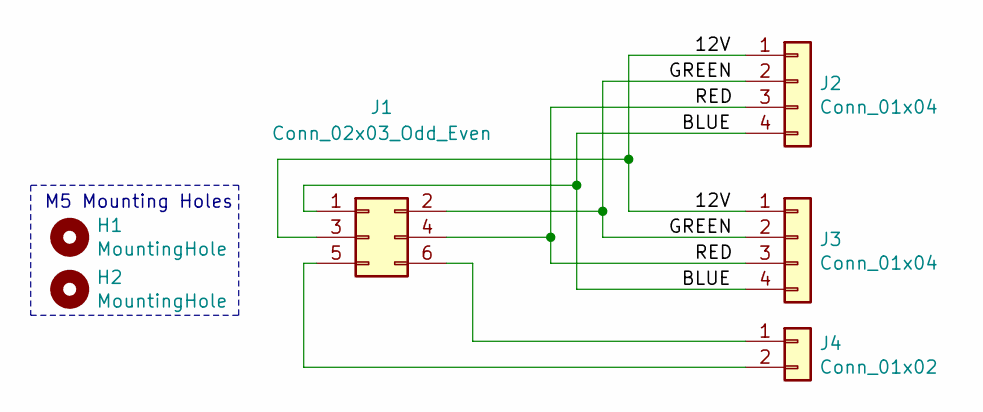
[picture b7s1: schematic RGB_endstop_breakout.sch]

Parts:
H1, H2: MountingHole; MountingHole_5.3mm_M5_Pad
J1: Conn_02x03_Odd_Even; IDC-Header_2x03_P2.54mm_Vertical
J2, J3: Conn_01x04; JST_XH_B4B-XH-A_1x04_P2.50mm_Vertical
J4: Conn_01x02; JST_XH_B2B-XH-A_1x02_P2.50mm_Vertical

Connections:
/12V: J1.3, J2.1, J3.1
/BLUE: J1.1, J2.4, J3.4
/GREEN: J1.2, J2.2, J3.2
/RED: J1.4, J2.3, J3.3
unnamed: J1.5, J4.2
unnamed: J1.6, J4.1

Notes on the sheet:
M5 Mounting Holes

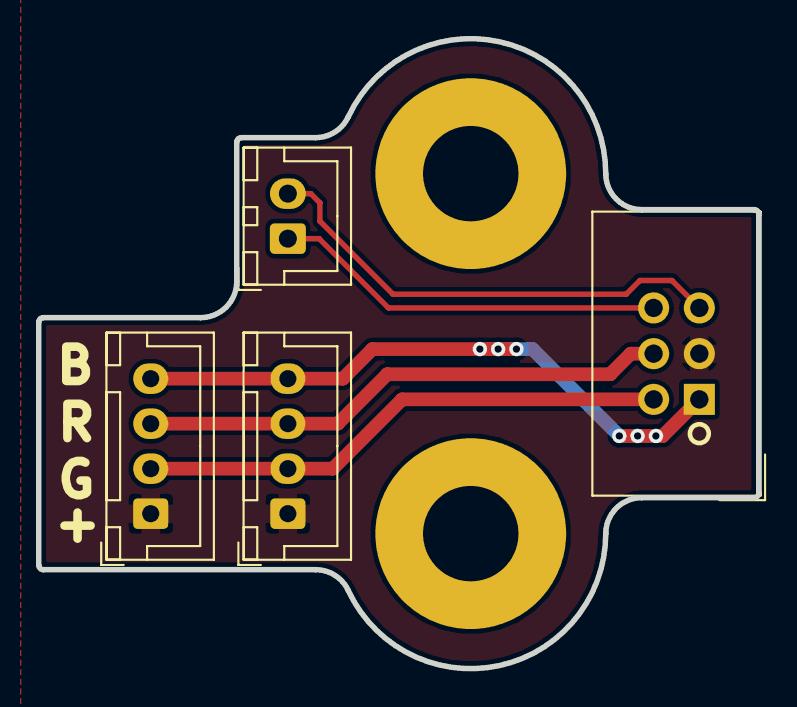
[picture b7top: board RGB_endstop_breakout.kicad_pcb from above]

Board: 2 copper layers, 40.0 x 35.0 mm, 6 parts (0 on the bottom side), 6 nets.

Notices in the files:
Firmware/Marlin-stepUP/Marlin-2.0.x/Marlin/src/lcd/ultralcd.h:
Copyright (c) 2020 MarlinFirmware [https://github.com/MarlinFirmware/Marlin]
Copyright (c) 2011 Camiel Gubbels / Erik van der Zalm
This program is free software: you can redistribute it and/or modify
it under the terms of the GNU General Public License as published by
the Free Software Foundation, either version 3 of the License, or
(at your option) any later version.
